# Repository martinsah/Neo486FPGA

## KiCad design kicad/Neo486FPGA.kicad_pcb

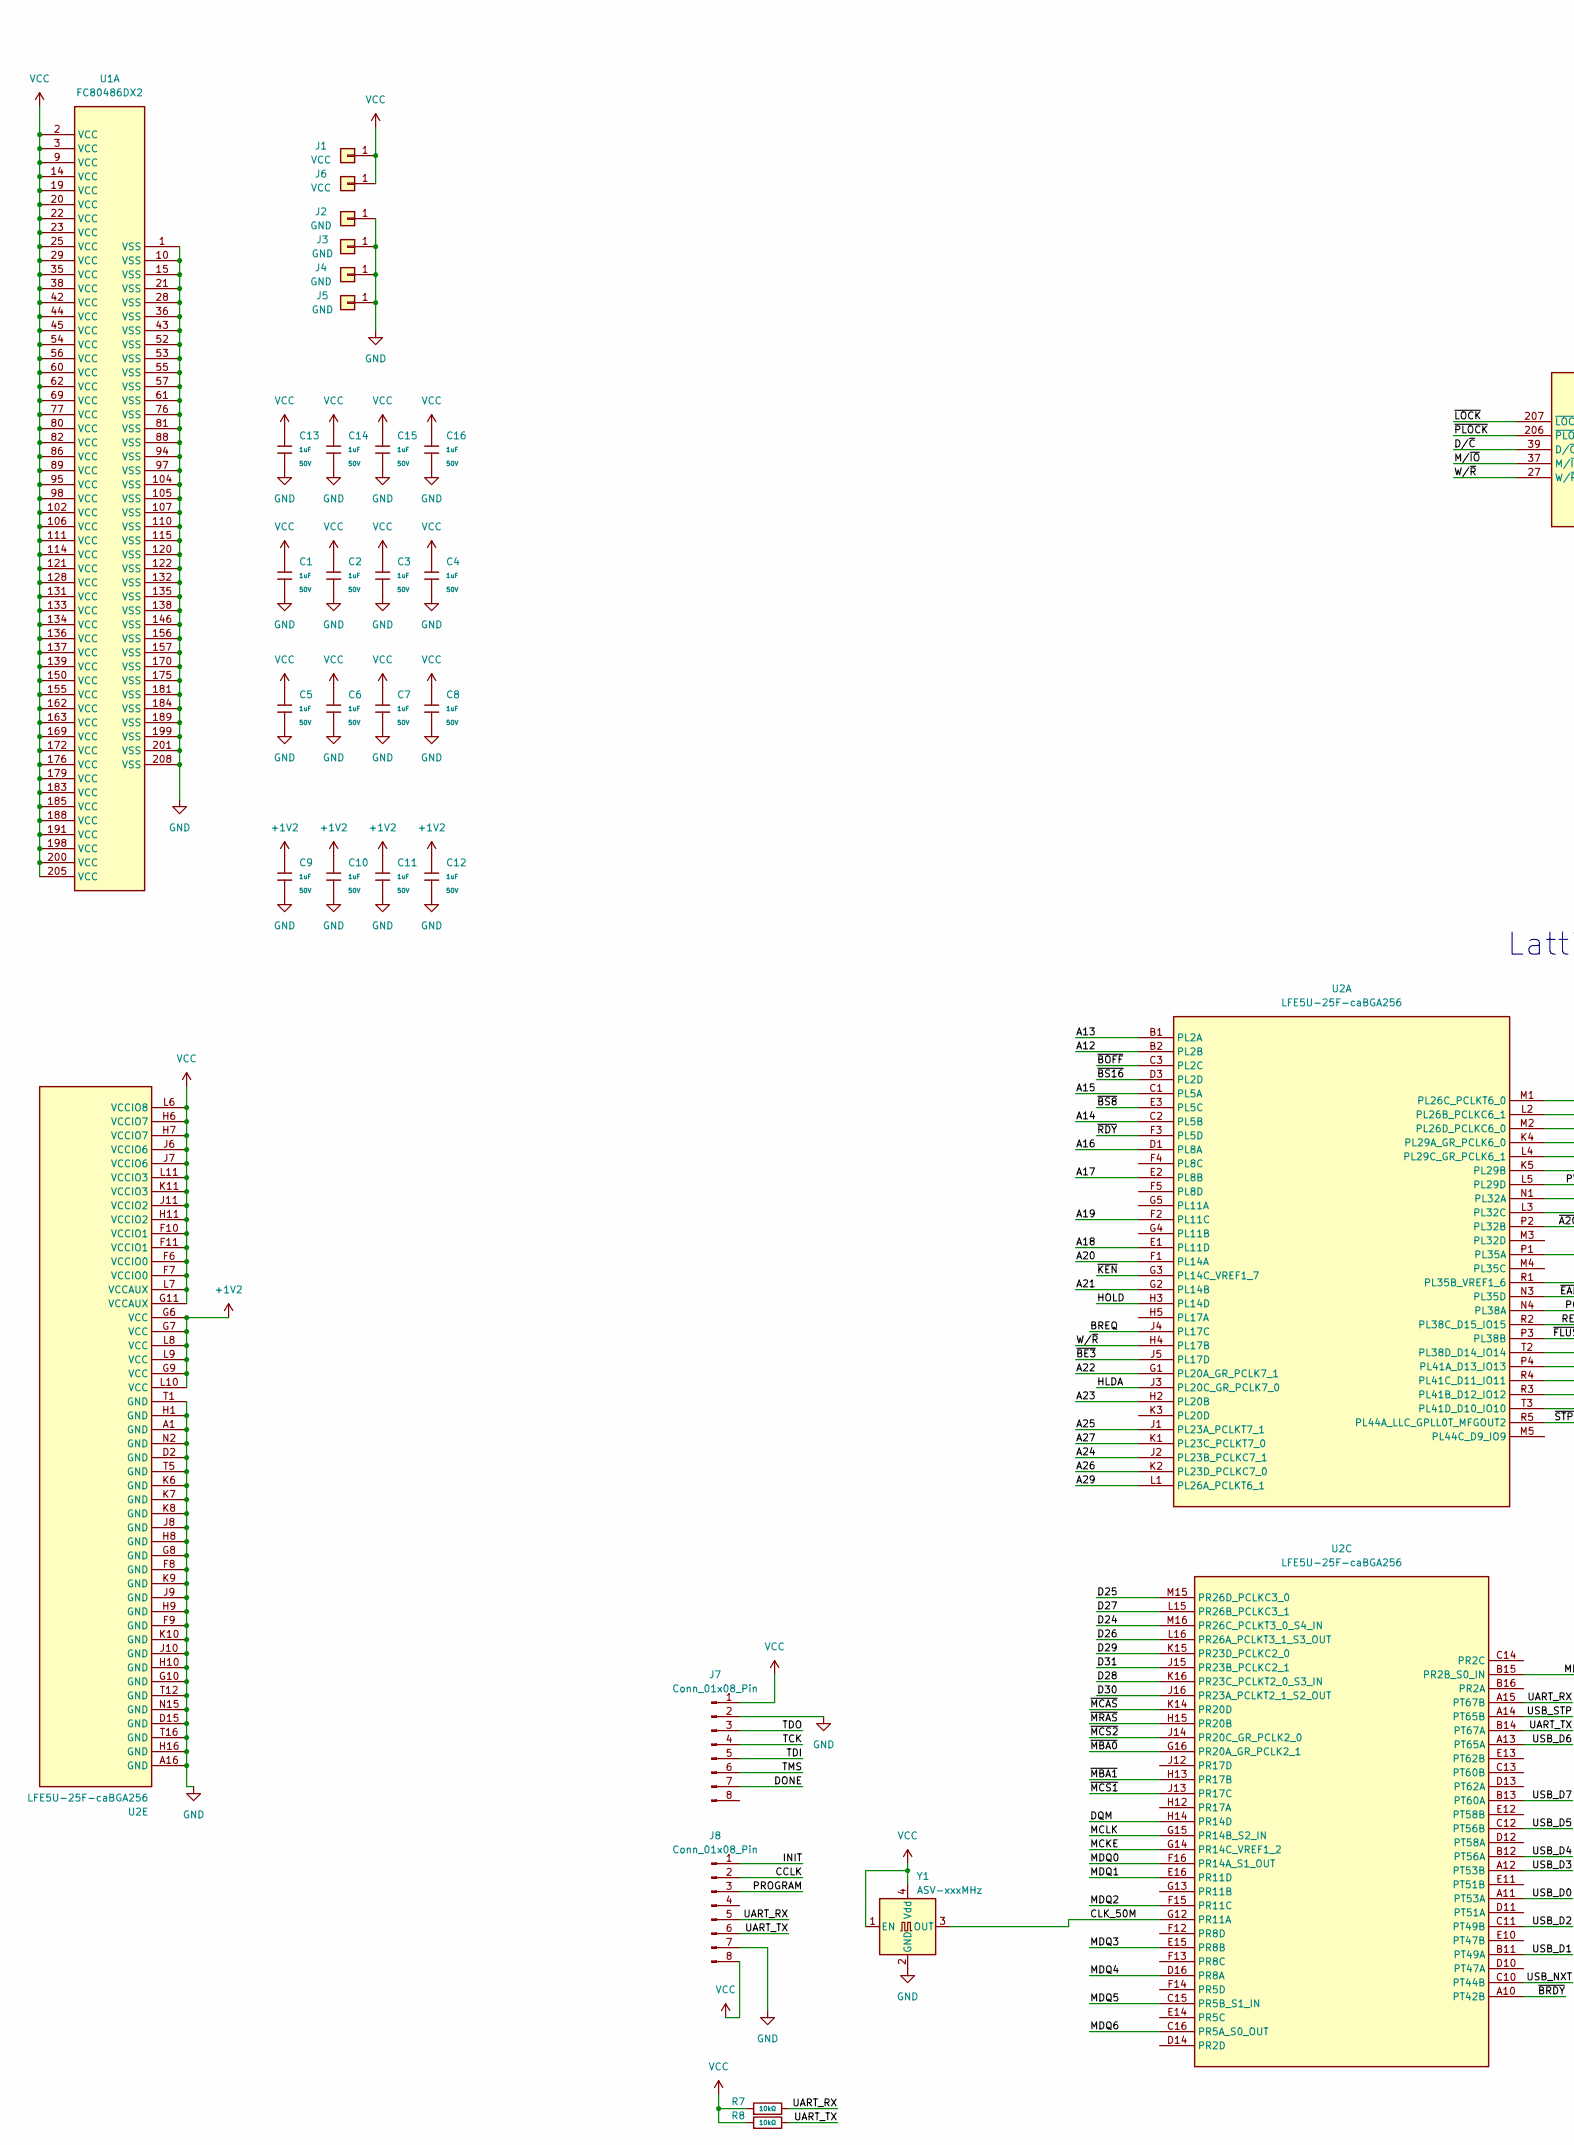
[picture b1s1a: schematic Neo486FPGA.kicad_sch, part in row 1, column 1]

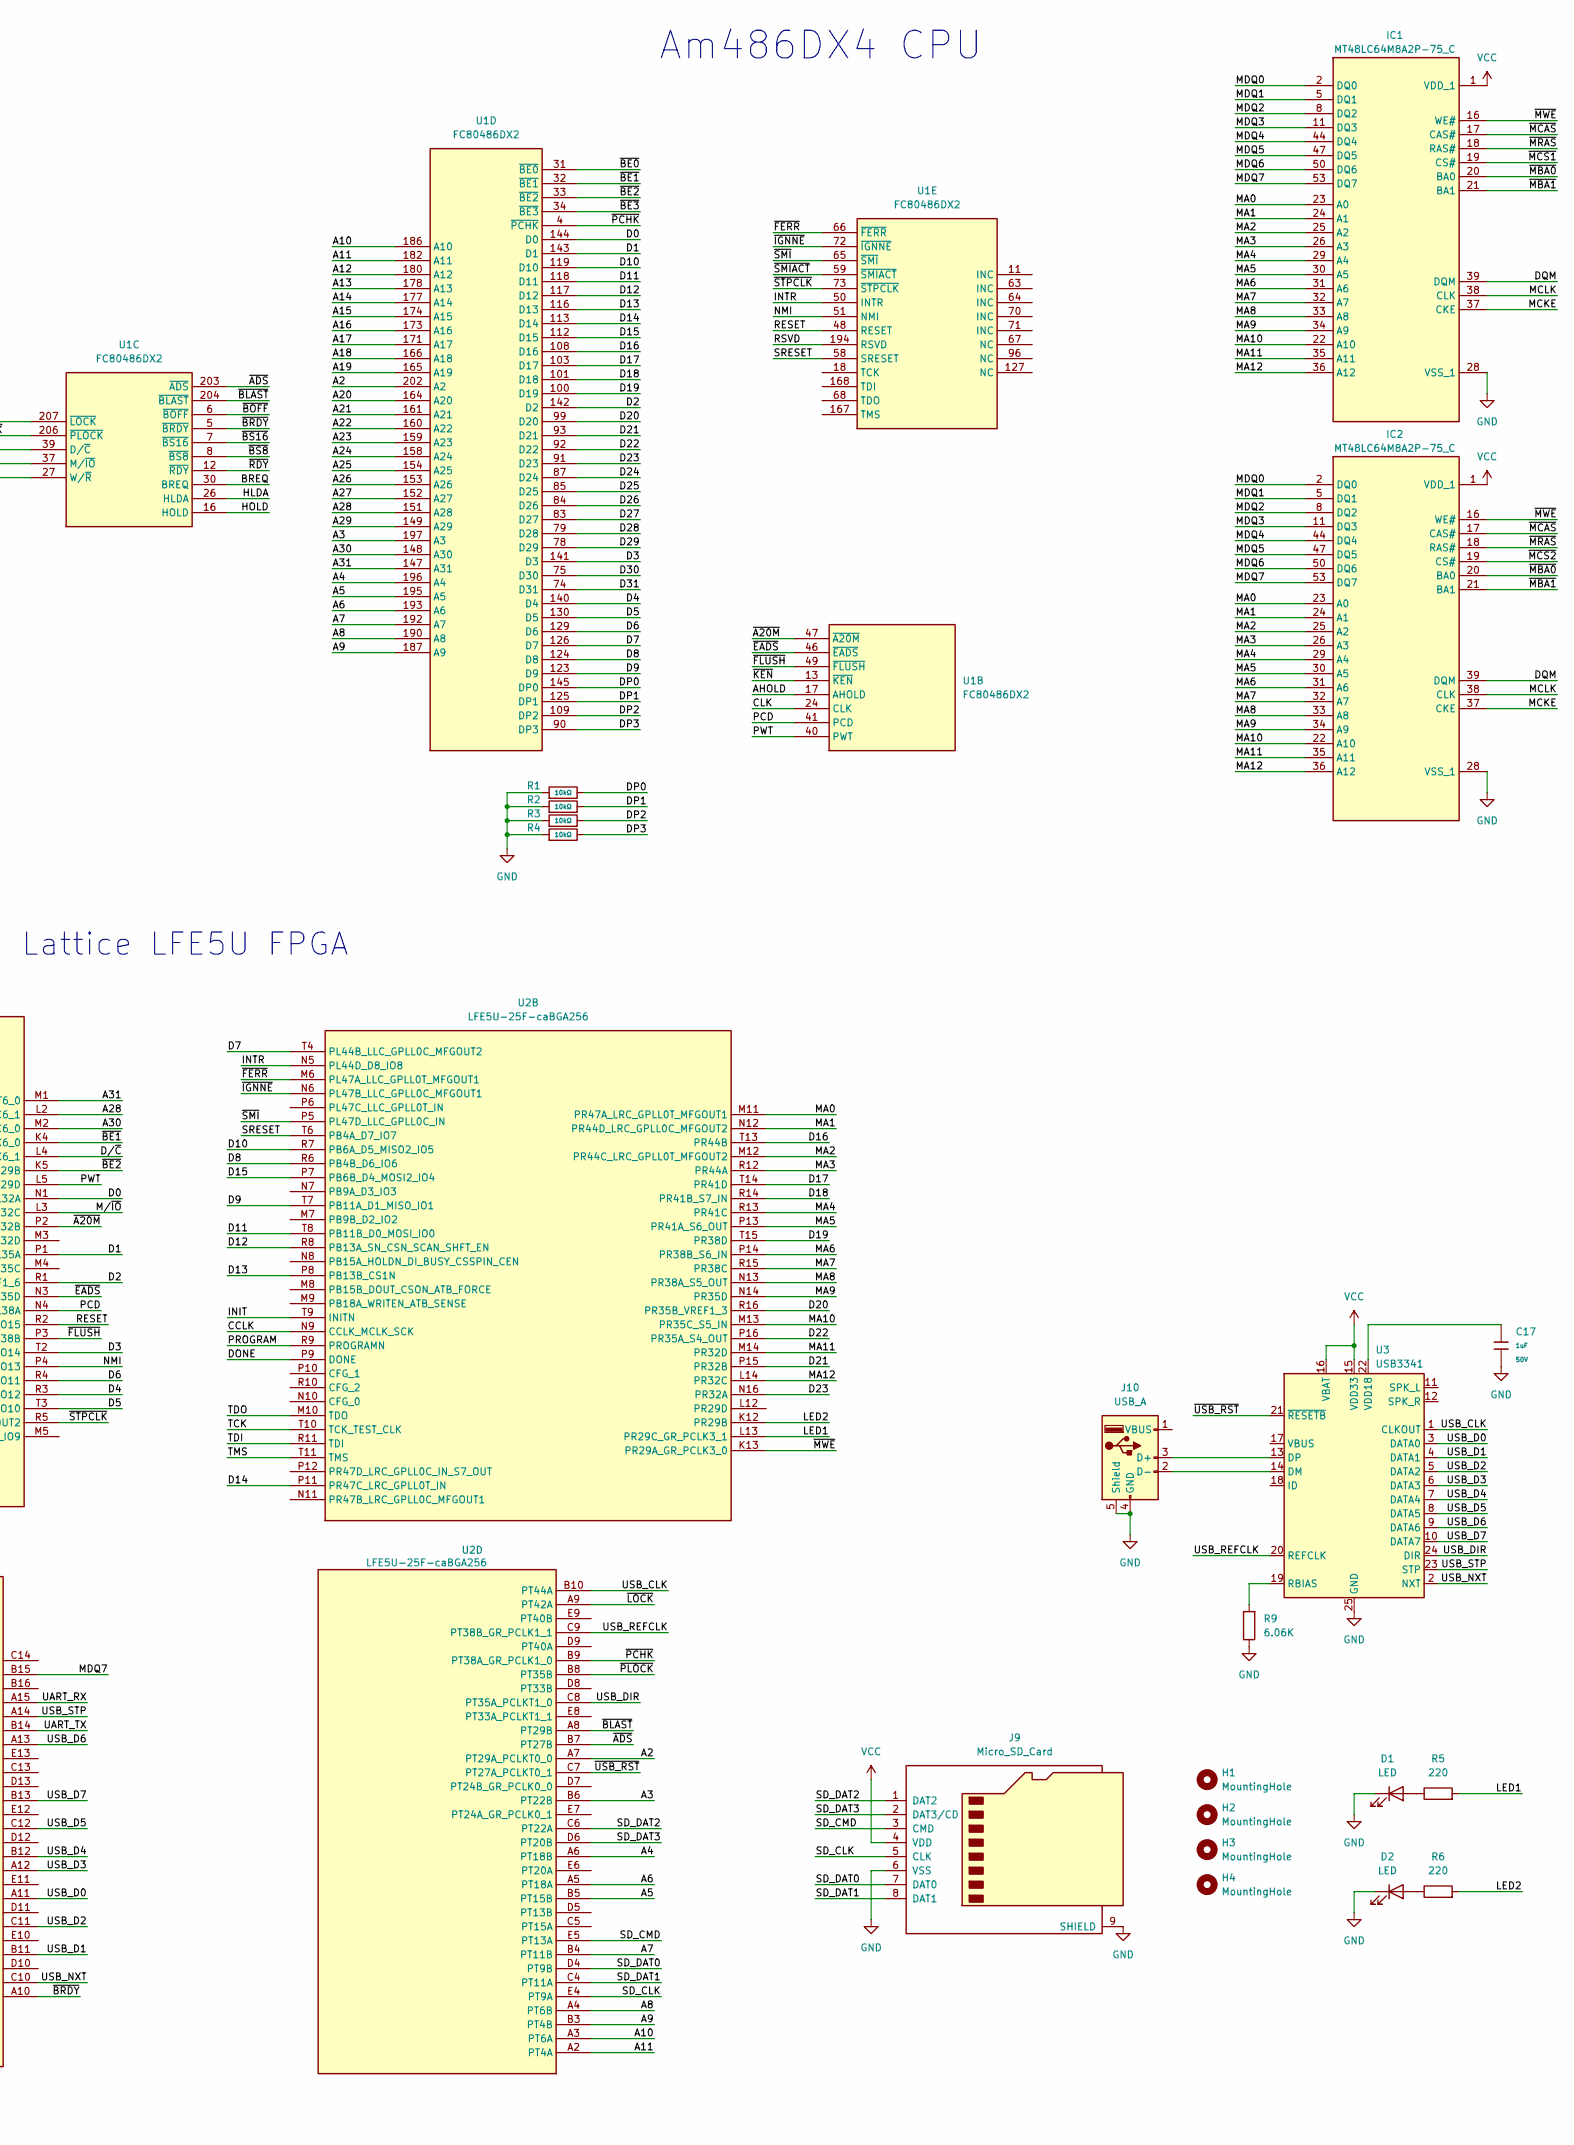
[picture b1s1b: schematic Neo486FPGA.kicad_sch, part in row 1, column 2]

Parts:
C1, C2, C3, C4, C5, C6, C7, C8, C9, C10, C11, C12, C13, C14, C15, C16, C17: 1uF; C_0603; Voltage Rated 50V; Tolerance ±10%; Part CL10A105KB8NNNC; LCSC C15849
D1, D2: LED; LED_0805_2012Metric
H1, H2, H3, H4: MountingHole; MountingHole_2.7mm_M2.5_DIN965_Pad
IC1, IC2: MT48LC64M8A2P-75_C; SOP80P1176X120-54N; Mouser Part Number 913-MT48LC64M8A2P75C
J1, J6: VCC; SolderWirePad_1x01_SMD_1.5x3mm
J2, J3, J4, J5: GND; SolderWirePad_1x01_SMD_1.5x3mm
J7, J8: Conn_01x08_Pin; PinHeader_1x08_P2.54mm_Vertical
J9: Micro_SD_Card; microSD_HC_Wuerth_693072010801
J10: USB_A; USB_A_Molex_67643_Horizontal
R1, R2, R3, R4, R7, R8: 10kΩ; R_0603; Overload Voltage (Max) 75V; Tolerance ±1%; Part 0603WAF1002T5E; LCSC C25804
R5, R6: 220; R_0603_1608Metric
R9: 6.06K; R_0603_1608Metric
U1: FC80486DX2; PQFP-208_28x28mm_P0.5mm
U2: LFE5U-25F-caBGA256; BGA-256_14.0x14.0mm_Layout16x16_P0.8mm_Ball0.45mm_Pad0.32mm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
U3: USB3341; QFN-24-1EP_4x4mm_P0.5mm_EP2.6x2.6mm
Y1: ASV-xxxMHz; Oscillator_SMD_Abracon_ASV-4Pin_7.0x5.1mm

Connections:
+1V2: C9.1, C10.1, C11.1, C12.1, U2.G6 (VCC), U2.G7 (VCC), U2.G9 (VCC), U2.L8 (VCC), U2.L9 (VCC), U2.L10 (VCC)
/A2: U1.202 (A2), U2.A7 (PT29A_PCLKT0_0)
/A3: U1.197 (A3), U2.B6 (PT22B)
/A4: U1.196 (A4), U2.A6 (PT18B)
/A5: U1.195 (A5), U2.B5 (PT15B)
/A6: U1.193 (A6), U2.A5 (PT18A)
/A7: U1.192 (A7), U2.B4 (PT11B)
/A8: U1.190 (A8), U2.A4 (PT6B)
/A9: U1.187 (A9), U2.B3 (PT4B)
/A10: U1.186 (A10), U2.A3 (PT6A)
/A11: U1.182 (A11), U2.A2 (PT4A)
/A12: U1.180 (A12), U2.B2 (PL2B)
/A13: U1.178 (A13), U2.B1 (PL2A)
/A14: U1.177 (A14), U2.C2 (PL5B)
/A15: U1.174 (A15), U2.C1 (PL5A)
/A16: U1.173 (A16), U2.D1 (PL8A)
/A17: U1.171 (A17), U2.E2 (PL8B)
/A18: U1.166 (A18), U2.E1 (PL11D)
/A19: U1.165 (A19), U2.F2 (PL11C)
/A20: U1.164 (A20), U2.F1 (PL14A)
/A21: U1.161 (A21), U2.G2 (PL14B)
/A22: U1.160 (A22), U2.G1 (PL20A_GR_PCLK7_1)
/A23: U1.159 (A23), U2.H2 (PL20B)
/A24: U1.158 (A24), U2.J2 (PL23B_PCLKC7_1)
/A25: U1.154 (A25), U2.J1 (PL23A_PCLKT7_1)
/A26: U1.153 (A26), U2.K2 (PL23D_PCLKC7_0)
/A27: U1.152 (A27), U2.K1 (PL23C_PCLKT7_0)
/A28: U1.151 (A28), U2.L2 (PL26B_PCLKC6_1)
/A29: U1.149 (A29), U2.L1 (PL26A_PCLKT6_1)
/A30: U1.148 (A30), U2.M2 (PL26D_PCLKC6_0)
/A31: U1.147 (A31), U2.M1 (PL26C_PCLKT6_0)
/AHOLD: U1.17 (AHOLD)
/BREQ: U1.30 (BREQ), U2.J4 (PL17C)
/CCLK: J8.2, U2.N9 (CCLK_MCLK_SCK)
/CLK: U1.24 (CLK)
/CLK_50M: U2.G12 (PR11A), Y1.3 (OUT)
/D0: U1.144 (D0), U2.N1 (PL32A)
/D1: U1.143 (D1), U2.P1 (PL35A)
/D2: U1.142 (D2), U2.R1 (PL35B_VREF1_6)
/D3: U1.141 (D3), U2.T2 (PL38D_D14_IO14)
/D4: U1.140 (D4), U2.R3 (PL41B_D12_IO12)
/D5: U1.130 (D5), U2.T3 (PL41D_D10_IO10)
/D6: U1.129 (D6), U2.R4 (PL41C_D11_IO11)
/D7: U1.126 (D7), U2.T4 (PL44B_LLC_GPLL0C_MFGOUT2)
/D8: U1.124 (D8), U2.R6 (PB4B_D6_IO6)
/D9: U1.123 (D9), U2.T7 (PB11A_D1_MISO_IO1)
/D10: U1.119 (D10), U2.R7 (PB6A_D5_MISO2_IO5)
/D11: U1.118 (D11), U2.T8 (PB11B_D0_MOSI_IO0)
/D12: U1.117 (D12), U2.R8 (PB13A_SN_CSN_SCAN_SHFT_EN)
/D13: U1.116 (D13), U2.P8 (PB13B_CS1N)
/D14: U1.113 (D14), U2.P11 (PR47C_LRC_GPLL0T_IN)
/D15: U1.112 (D15), U2.P7 (PB6B_D4_MOSI2_IO4)
/D16: U1.108 (D16), U2.T13 (PR44B)
/D17: U1.103 (D17), U2.T14 (PR41D)
/D18: U1.101 (D18), U2.R14 (PR41B_S7_IN)
/D19: U1.100 (D19), U2.T15 (PR38D)
/D20: U1.99 (D20), U2.R16 (PR35B_VREF1_3)
/D21: U1.93 (D21), U2.P15 (PR32B)
/D22: U1.92 (D22), U2.P16 (PR35A_S4_OUT)
/D23: U1.91 (D23), U2.N16 (PR32A)
/D24: U1.87 (D24), U2.M16 (PR26C_PCLKT3_0_S4_IN)
/D25: U1.85 (D25), U2.M15 (PR26D_PCLKC3_0)
/D26: U1.84 (D26), U2.L16 (PR26A_PCLKT3_1_S3_OUT)
/D27: U1.83 (D27), U2.L15 (PR26B_PCLKC3_1)
/D28: U1.79 (D28), U2.K16 (PR23C_PCLKT2_0_S3_IN)
/D29: U1.78 (D29), U2.K15 (PR23D_PCLKC2_0)
/D30: U1.75 (D30), U2.J16 (PR23A_PCLKT2_1_S2_OUT)
/D31: U1.74 (D31), U2.J15 (PR23B_PCLKC2_1)
/DONE: J7.7, U2.P9 (DONE)
/DP0: R1.2, U1.145 (DP0)
/DP1: R2.2, U1.125 (DP1)
/DP2: R3.2, U1.109 (DP2)
/DP3: R4.2, U1.90 (DP3)
/DQM: IC1.39 (DQM), IC2.39 (DQM), U2.H14 (PR14D)
/D/~C: U1.39 (D/~C), U2.L4 (PL29C_GR_PCLK6_1)
/HLDA: U1.26 (HLDA), U2.J3 (PL20C_GR_PCLK7_0)
/HOLD: U1.16 (HOLD), U2.H3 (PL14D)
/INIT: J8.1, U2.T9 (INITN)
/INTR: U1.50 (INTR), U2.N5 (PL44D_D8_IO8)
/LED1: R5.2, U2.L13 (PR29C_GR_PCLK3_1)
/LED2: R6.2, U2.K12 (PR29B)
/MA0: IC1.23 (A0), IC2.23 (A0), U2.M11 (PR47A_LRC_GPLL0T_MFGOUT1)
/MA1: IC1.24 (A1), IC2.24 (A1), U2.N12 (PR44D_LRC_GPLL0C_MFGOUT2)
/MA2: IC1.25 (A2), IC2.25 (A2), U2.M12 (PR44C_LRC_GPLL0T_MFGOUT2)
/MA3: IC1.26 (A3), IC2.26 (A3), U2.R12 (PR44A)
/MA4: IC1.29 (A4), IC2.29 (A4), U2.R13 (PR41C)
/MA5: IC1.30 (A5), IC2.30 (A5), U2.P13 (PR41A_S6_OUT)
/MA6: IC1.31 (A6), IC2.31 (A6), U2.P14 (PR38B_S6_IN)
/MA7: IC1.32 (A7), IC2.32 (A7), U2.R15 (PR38C)
/MA8: IC1.33 (A8), IC2.33 (A8), U2.N13 (PR38A_S5_OUT)
/MA9: IC1.34 (A9), IC2.34 (A9), U2.N14 (PR35D)
/MA10: IC1.22 (A10), IC2.22 (A10), U2.M13 (PR35C_S5_IN)
/MA11: IC1.35 (A11), IC2.35 (A11), U2.M14 (PR32D)
/MA12: IC1.36 (A12), IC2.36 (A12), U2.L14 (PR32C)
/MCKE: IC1.37 (CKE), IC2.37 (CKE), U2.G14 (PR14C_VREF1_2)
/MCLK: IC1.38 (CLK), IC2.38 (CLK), U2.G15 (PR14B_S2_IN)
/MDQ0: IC1.2 (DQ0), IC2.2 (DQ0), U2.F16 (PR14A_S1_OUT)
/MDQ1: IC1.5 (DQ1), IC2.5 (DQ1), U2.E16 (PR11D)
/MDQ2: IC1.8 (DQ2), IC2.8 (DQ2), U2.F15 (PR11C)
/MDQ3: IC1.11 (DQ3), IC2.11 (DQ3), U2.E15 (PR8B)
/MDQ4: IC1.44 (DQ4), IC2.44 (DQ4), U2.D16 (PR8A)
/MDQ5: IC1.47 (DQ5), IC2.47 (DQ5), U2.C15 (PR5B_S1_IN)
/MDQ6: IC1.50 (DQ6), IC2.50 (DQ6), U2.C16 (PR5A_S0_OUT)
/MDQ7: IC1.53 (DQ7), IC2.53 (DQ7), U2.B15 (PR2B_S0_IN)
/M/~IO: U1.37 (M/~IO), U2.L3 (PL32C)
/NMI: U1.51 (NMI), U2.P4 (PL41A_D13_IO13)
/PCD: U1.41 (PCD), U2.N4 (PL38A)
/PROGRAM: J8.3, U2.R9 (PROGRAMN)
/PWT: U1.40 (PWT), U2.L5 (PL29D)
/RESET: U1.48 (RESET), U2.R2 (PL38C_D15_IO15)
/RSVD: U1.194 (RSVD)
/SD_CLK: J9.5 (CLK), U2.E4 (PT9A)
/SD_CMD: J9.3 (CMD), U2.E5 (PT13A)
/SD_DAT0: J9.7 (DAT0), U2.D4 (PT9B)
/SD_DAT1: J9.8 (DAT1), U2.C4 (PT11A)
/SD_DAT2: J9.1 (DAT2), U2.C6 (PT22A)
/SD_DAT3: J9.2 (DAT3/CD), U2.D6 (PT20B)
/SRESET: U1.58 (SRESET), U2.T6 (PB4A_D7_IO7)
/TCK: J7.4, U2.T10 (TCK_TEST_CLK)
/TDI: J7.5, U2.R11 (TDI)
/TDO: J7.3, U2.M10 (TDO)
/TMS: J7.6, U2.T11 (TMS)
/UART_RX: J8.5, R7.2, U2.A15 (PT67B)
/UART_TX: J8.6, R8.2, U2.B14 (PT67A)
/USB_CLK: U2.B10 (PT44A), U3.1 (CLKOUT)
/USB_D0: U2.A11 (PT53A), U3.3 (DATA0)
/USB_D1: U2.B11 (PT49A), U3.4 (DATA1)
/USB_D2: U2.C11 (PT49B), U3.5 (DATA2)
/USB_D3: U2.A12 (PT53B), U3.6 (DATA3)
/USB_D4: U2.B12 (PT56A), U3.7 (DATA4)
/USB_D5: U2.C12 (PT56B), U3.8 (DATA5)
/USB_D6: U2.A13 (PT65A), U3.9 (DATA6)
/USB_D7: U2.B13 (PT60A), U3.10 (DATA7)
/USB_DIR: U2.C8 (PT35A_PCLKT1_0), U3.24 (DIR)
/USB_NXT: U2.C10 (PT44B), U3.2 (NXT)
/USB_REFCLK: U2.C9 (PT38B_GR_PCLK1_1), U3.20 (REFCLK)
/USB_STP: U2.A14 (PT65B), U3.23 (STP)
/W/~R: U1.27 (W/~R), U2.H4 (PL17B)
/~A20M: U1.47 (~A20M), U2.P2 (PL32B)
/~ADS: U1.203 (~ADS), U2.B7 (PT27B)
/~BE0: U1.31 (~BE0)
/~BE1: U1.32 (~BE1), U2.K4 (PL29A_GR_PCLK6_0)
/~BE2: U1.33 (~BE2), U2.K5 (PL29B)
/~BE3: U1.34 (~BE3), U2.J5 (PL17D)
/~BLAST: U1.204 (~BLAST), U2.A8 (PT29B)
/~BOFF: U1.6 (~BOFF), U2.C3 (PL2C)
/~BRDY: U1.5 (~BRDY), U2.A10 (PT42B)
/~BS8: U1.8 (~BS8), U2.E3 (PL5C)
/~BS16: U1.7 (~BS16), U2.D3 (PL2D)
/~EADS: U1.46 (~EADS), U2.N3 (PL35D)
/~FERR: U1.66 (~FERR), U2.M6 (PL47A_LLC_GPLL0T_MFGOUT1)
/~FLUSH: U1.49 (~FLUSH), U2.P3 (PL38B)
/~IGNNE: U1.72 (~IGNNE), U2.N6 (PL47B_LLC_GPLL0C_MFGOUT1)
/~KEN: U1.13 (~KEN), U2.G3 (PL14C_VREF1_7)
/~LOCK: U1.207 (~LOCK), U2.A9 (PT42A)
/~MBA0: IC1.20 (BA0), IC2.20 (BA0), U2.G16 (PR20A_GR_PCLK2_1)
/~MBA1: IC1.21 (BA1), IC2.21 (BA1), U2.H13 (PR17B)
/~MCAS: IC1.17 (CAS#), IC2.17 (CAS#), U2.K14 (PR20D)
/~MCS1: IC1.19 (CS#), U2.J13 (PR17C)
/~MCS2: IC2.19 (CS#), U2.J14 (PR20C_GR_PCLK2_0)
/~MRAS: IC1.18 (RAS#), IC2.18 (RAS#), U2.H15 (PR20B)
/~MWE: IC1.16 (WE#), IC2.16 (WE#), U2.K13 (PR29A_GR_PCLK3_0)
/~PCHK: U1.4 (~PCHK), U2.B9 (PT38A_GR_PCLK1_0)
/~PLOCK: U1.206 (~PLOCK), U2.B8 (PT35B)
/~RDY: U1.12 (~RDY), U2.F3 (PL5D)
/~SMIACT: U1.59 (~SMIACT)
/~SMI: U1.65 (~SMI), U2.P5 (PL47D_LLC_GPLL0C_IN)
/~STPCLK: U1.73 (~STPCLK), U2.R5 (PL44A_LLC_GPLL0T_MFGOUT2)
/~USB_RST: U2.C7 (PT27A_PCLKT0_1), U3.21 (~RESETB)
GND: C1.2, C2.2, C3.2, C4.2, C5.2, C6.2, C7.2, C8.2, C9.2, C10.2, C11.2, C12.2, C13.2, C14.2, C15.2, C16.2, C17.2, D1.1 (K), D2.1 (K), IC1.6 (VSSQ_1), IC1.12 (VSSQ_2), IC1.28 (VSS_1), IC1.41 (VSS_2), IC1.46 (VSSQ_3), IC1.52 (VSSQ_4), IC1.54 (VSS_3), IC2.6 (VSSQ_1), IC2.12 (VSSQ_2), IC2.28 (VSS_1), IC2.41 (VSS_2), IC2.46 (VSSQ_3), IC2.52 (VSSQ_4), IC2.54 (VSS_3), J2.1, J3.1, J4.1, J5.1, J7.2, J8.7, J9.6 (VSS), J9.9 (SHIELD), J10.4 (GND), J10.5 (Shield), R1.1, R2.1, R3.1, R4.1, R9.1, U1.1 (VSS), U1.10 (VSS), U1.15 (VSS), U1.21 (VSS), U1.28 (VSS), U1.36 (VSS), U1.43 (VSS), U1.52 (VSS), U1.53 (VSS), U1.55 (VSS), U1.57 (VSS), U1.61 (VSS), U1.76 (VSS), U1.81 (VSS), U1.88 (VSS), U1.94 (VSS), U1.97 (VSS), U1.104 (VSS), U1.105 (VSS), U1.107 (VSS), U1.110 (VSS), U1.115 (VSS), U1.120 (VSS), U1.122 (VSS), U1.132 (VSS), U1.135 (VSS), U1.138 (VSS), U1.146 (VSS), U1.156 (VSS), U1.157 (VSS), U1.170 (VSS), U1.175 (VSS), U1.181 (VSS), U1.184 (VSS), U1.189 (VSS), U1.199 (VSS), U1.201 (VSS), U1.208 (VSS), U2.A1 (GND), U2.A16 (GND), U2.D2 (GND), U2.D15 (GND), U2.F8 (GND), U2.F9 (GND), U2.G8 (GND), U2.G10 (GND), U2.H1 (GND), U2.H8 (GND), U2.H9 (GND), U2.H10 (GND), U2.H16 (GND), U2.J8 (GND), U2.J9 (GND), U2.J10 (GND), U2.K6 (GND), U2.K7 (GND), U2.K8 (GND), U2.K9 (GND), U2.K10 (GND), U2.N2 (GND), U2.N15 (GND), U2.T1 (GND), U2.T5 (GND), U2.T12 (GND), U2.T16 (GND), U3.25 (GND), Y1.2 (GND)
unnamed: D1.2 (A), R5.1
unnamed: D2.2 (A), R6.1
unnamed: J10.3 (D+), U3.13 (DP)
unnamed: J10.2 (D-), U3.14 (DM)
unnamed: R9.2, U3.19 (RBIAS)
unnamed: C17.1, U3.22 (VDD18)
VCC: C1.1, C2.1, C3.1, C4.1, C5.1, C6.1, C7.1, C8.1, C13.1, C14.1, C15.1, C16.1, IC1.1 (VDD_1), IC1.3 (VDDQ_1), IC1.9 (VDDQ_2), IC1.14 (VDD_2), IC1.27 (VDD_3), IC1.43 (VDDQ_3), IC1.49 (VDDQ_4), IC2.1 (VDD_1), IC2.3 (VDDQ_1), IC2.9 (VDDQ_2), IC2.14 (VDD_2), IC2.27 (VDD_3), IC2.43 (VDDQ_3), IC2.49 (VDDQ_4), J1.1, J6.1, J7.1, J8.8, J9.4 (VDD), R7.1, R8.1, U1.2 (VCC), U1.3 (VCC), U1.9 (VCC), U1.14 (VCC), U1.19 (VCC), U1.20 (VCC), U1.22 (VCC), U1.23 (VCC), U1.25 (VCC), U1.29 (VCC), U1.35 (VCC), U1.38 (VCC), U1.42 (VCC), U1.44 (VCC), U1.45 (VCC), U1.54 (VCC), U1.56 (VCC), U1.60 (VCC), U1.62 (VCC), U1.69 (VCC), U1.77 (VCC), U1.80 (VCC), U1.82 (VCC), U1.86 (VCC), U1.89 (VCC), U1.95 (VCC), U1.98 (VCC), U1.102 (VCC), U1.106 (VCC), U1.111 (VCC), U1.114 (VCC), U1.121 (VCC), U1.128 (VCC), U1.131 (VCC), U1.133 (VCC), U1.134 (VCC), U1.136 (VCC), U1.137 (VCC), U1.139 (VCC), U1.150 (VCC), U1.155 (VCC), U1.162 (VCC), U1.163 (VCC), U1.169 (VCC), U1.172 (VCC), U1.176 (VCC), U1.179 (VCC), U1.183 (VCC), U1.185 (VCC), U1.188 (VCC), U1.191 (VCC), U1.198 (VCC), U1.200 (VCC), U1.205 (VCC), U2.F6 (VCCIO0), U2.F7 (VCCIO0), U2.F10 (VCCIO1), U2.F11 (VCCIO1), U2.G11 (VCCAUX), U2.H6 (VCCIO7), U2.H7 (VCCIO7), U2.H11 (VCCIO2), U2.J6 (VCCIO6), U2.J7 (VCCIO6), U2.J11 (VCCIO2), U2.K11 (VCCIO3), U2.L6 (VCCIO8), U2.L7 (VCCAUX), U2.L11 (VCCIO3), U3.15 (VDD33), U3.16 (VBAT), Y1.1 (EN), Y1.4 (Vdd)

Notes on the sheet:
Lattice LFE5U FPGA
Am486DX4 CPU

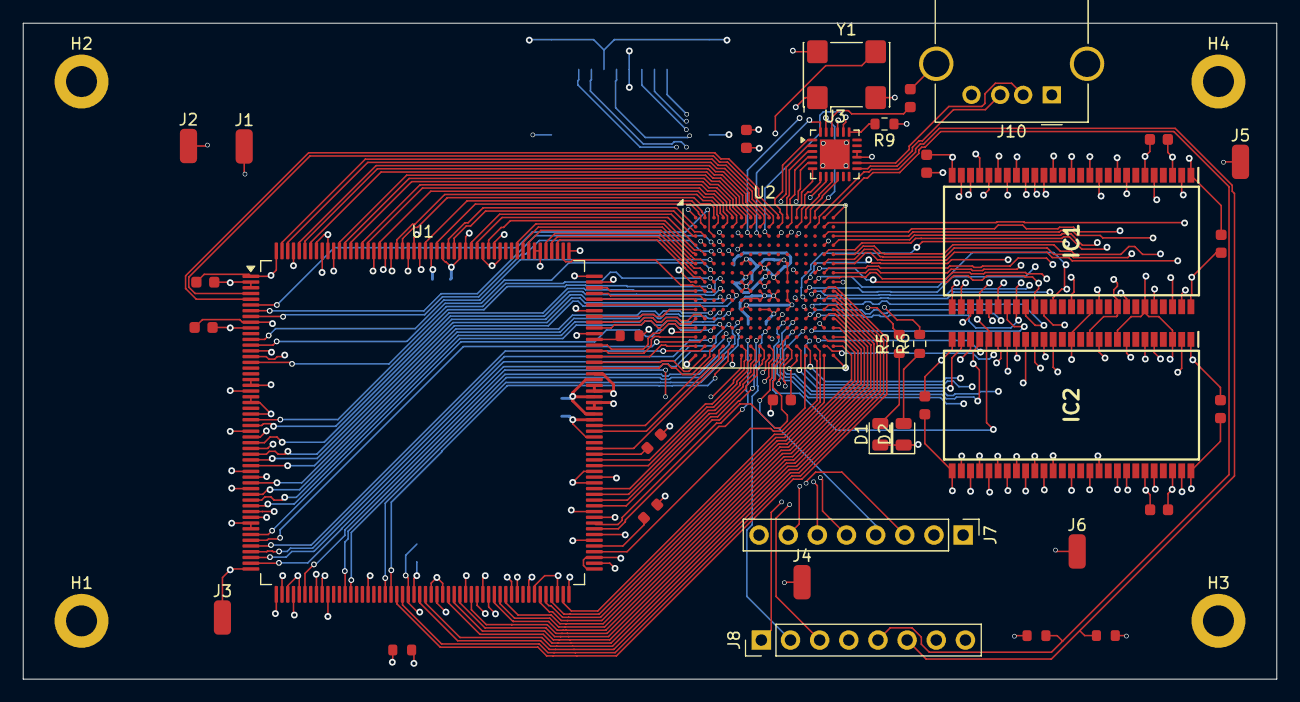
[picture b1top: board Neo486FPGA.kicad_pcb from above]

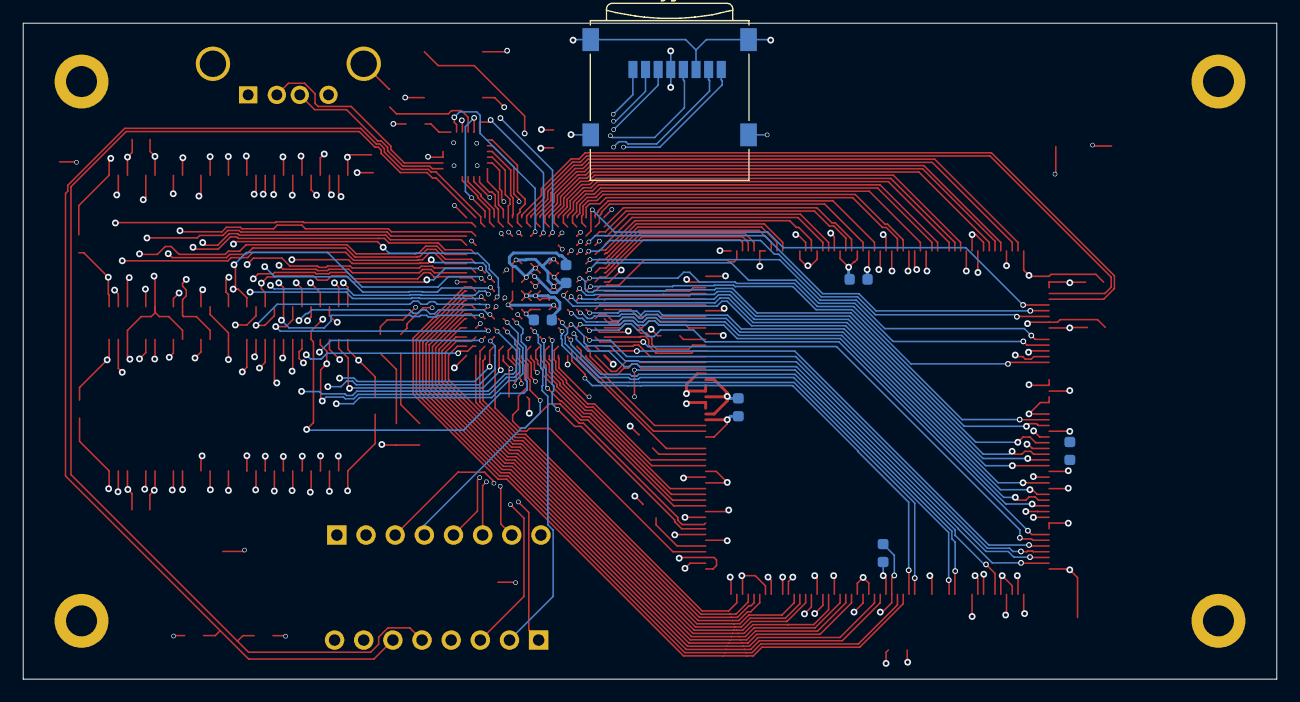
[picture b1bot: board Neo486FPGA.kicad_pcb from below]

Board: 4 copper layers, 109.2 x 57.1 mm, 48 parts (7 on the bottom side), 172 nets.

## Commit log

2026-03-24 Initial Add to repo - design is not ready for production!
